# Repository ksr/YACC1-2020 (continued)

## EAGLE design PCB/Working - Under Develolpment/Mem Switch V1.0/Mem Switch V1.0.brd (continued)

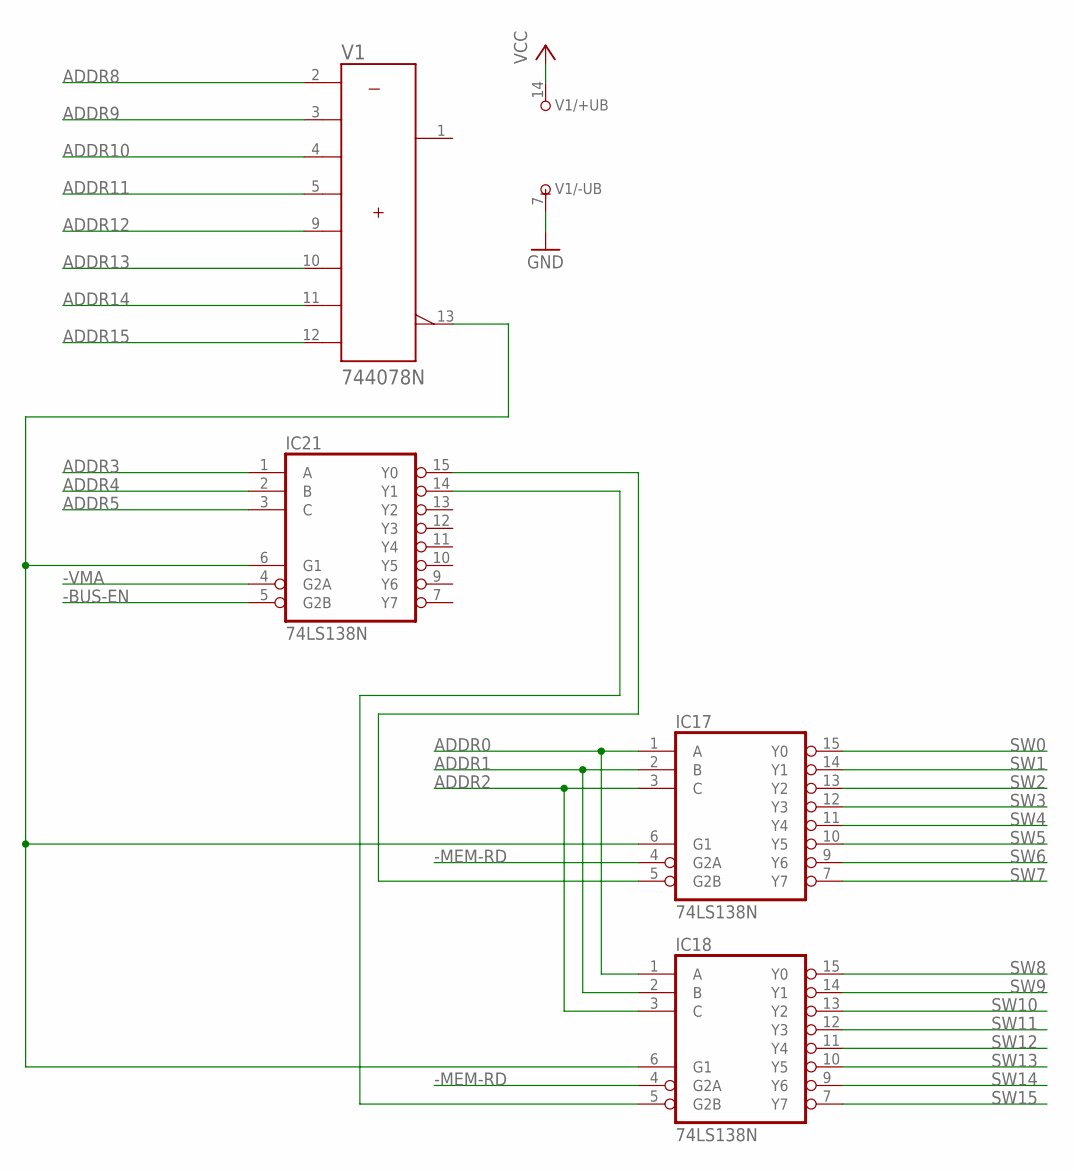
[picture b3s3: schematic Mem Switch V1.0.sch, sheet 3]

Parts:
IC17, IC18, IC21: 74LS138N; DIL16
V1: 744078N; DIL14

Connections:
-BUS-EN: IC21.5 (G2B); also elsewhere on the board
-MEM-RD: IC17.4 (G2A), IC18.4 (G2A); also elsewhere on the board
-VMA: IC21.4 (G2A); also elsewhere on the board
ADDR0: IC17.1 (A), IC18.1 (A); also elsewhere on the board
ADDR1: IC17.2 (B), IC18.2 (B); also elsewhere on the board
ADDR2: IC17.3 (C), IC18.3 (C); also elsewhere on the board
ADDR3: IC21.1 (A); also elsewhere on the board
ADDR4: IC21.2 (B); also elsewhere on the board
ADDR5: IC21.3 (C); also elsewhere on the board
ADDR8: V1.2 (A); also elsewhere on the board
ADDR9: V1.3 (B); also elsewhere on the board
ADDR10: V1.4 (C); also elsewhere on the board
ADDR11: V1.5 (D); also elsewhere on the board
ADDR12: V1.9 (E); also elsewhere on the board
ADDR13: V1.10 (F); also elsewhere on the board
ADDR14: V1.11 (G); also elsewhere on the board
ADDR15: V1.12 (H); also elsewhere on the board
GND: IC17.8 (GND), IC18.8 (GND), IC21.8 (GND), V1.7 (-UB); also elsewhere on the board
unnamed: IC17.5 (G2B), IC21.15 (Y0)
unnamed: IC18.5 (G2B), IC21.14 (Y1)
unnamed: IC17.6 (G1), IC18.6 (G1), IC21.6 (G1), V1.13 (W)
SW0: IC17.15 (Y0); also elsewhere on the board
SW1: IC17.14 (Y1); also elsewhere on the board
SW2: IC17.13 (Y2); also elsewhere on the board
SW3: IC17.12 (Y3); also elsewhere on the board
SW4: IC17.11 (Y4); also elsewhere on the board
SW5: IC17.10 (Y5); also elsewhere on the board
SW6: IC17.9 (Y6); also elsewhere on the board
SW7: IC17.7 (Y7); also elsewhere on the board
SW8: IC18.15 (Y0); also elsewhere on the board
SW9: IC18.14 (Y1); also elsewhere on the board
SW10: IC18.13 (Y2); also elsewhere on the board
SW11: IC18.12 (Y3); also elsewhere on the board
SW12: IC18.11 (Y4); also elsewhere on the board
SW13: IC18.10 (Y5); also elsewhere on the board
SW14: IC18.9 (Y6); also elsewhere on the board
SW15: IC18.7 (Y7); also elsewhere on the board
VCC: IC17.16 (VCC), IC18.16 (VCC), IC21.16 (VCC), V1.14 (+UB); also elsewhere on the board

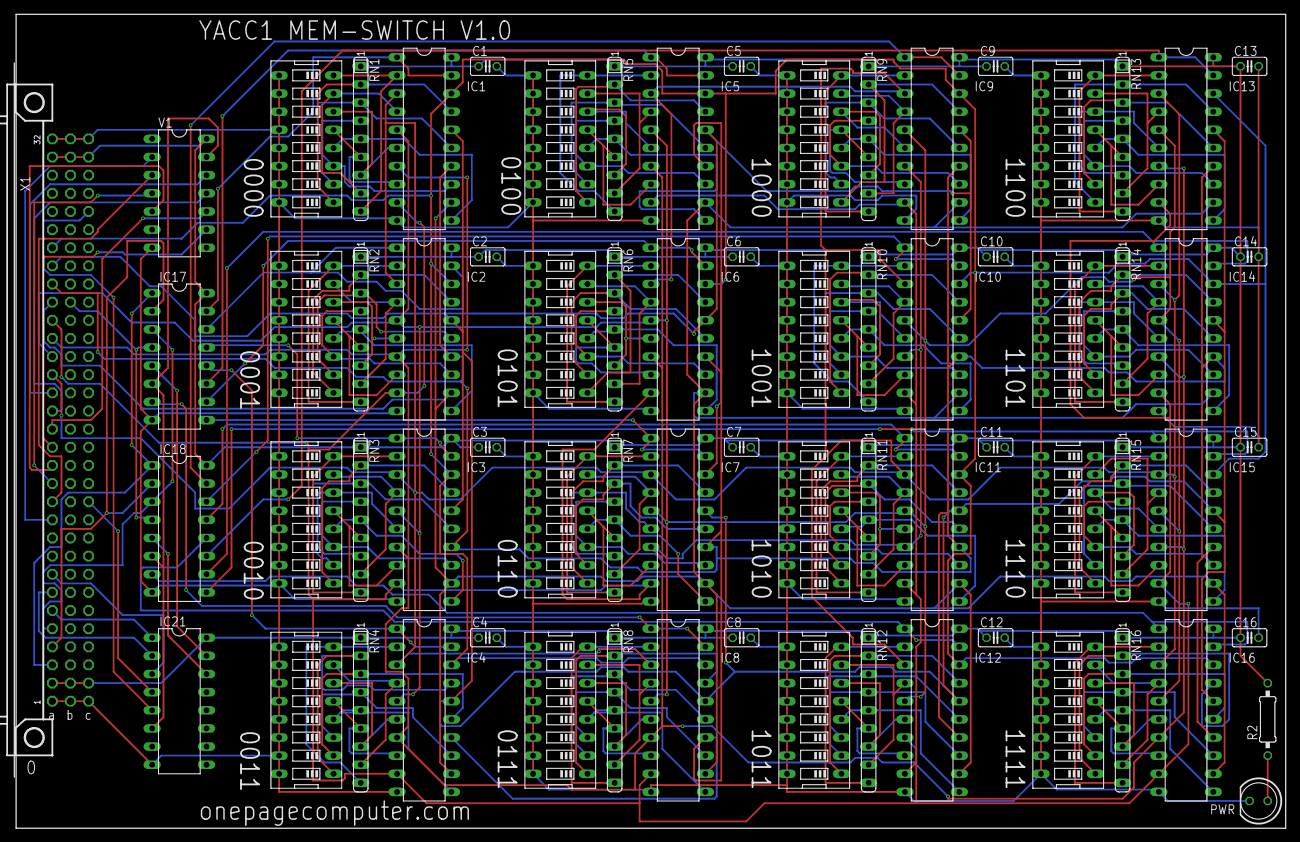
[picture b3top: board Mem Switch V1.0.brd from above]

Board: 2 copper layers, 177.8 x 114.0 mm, 71 parts (0 on the bottom side), 175 nets.

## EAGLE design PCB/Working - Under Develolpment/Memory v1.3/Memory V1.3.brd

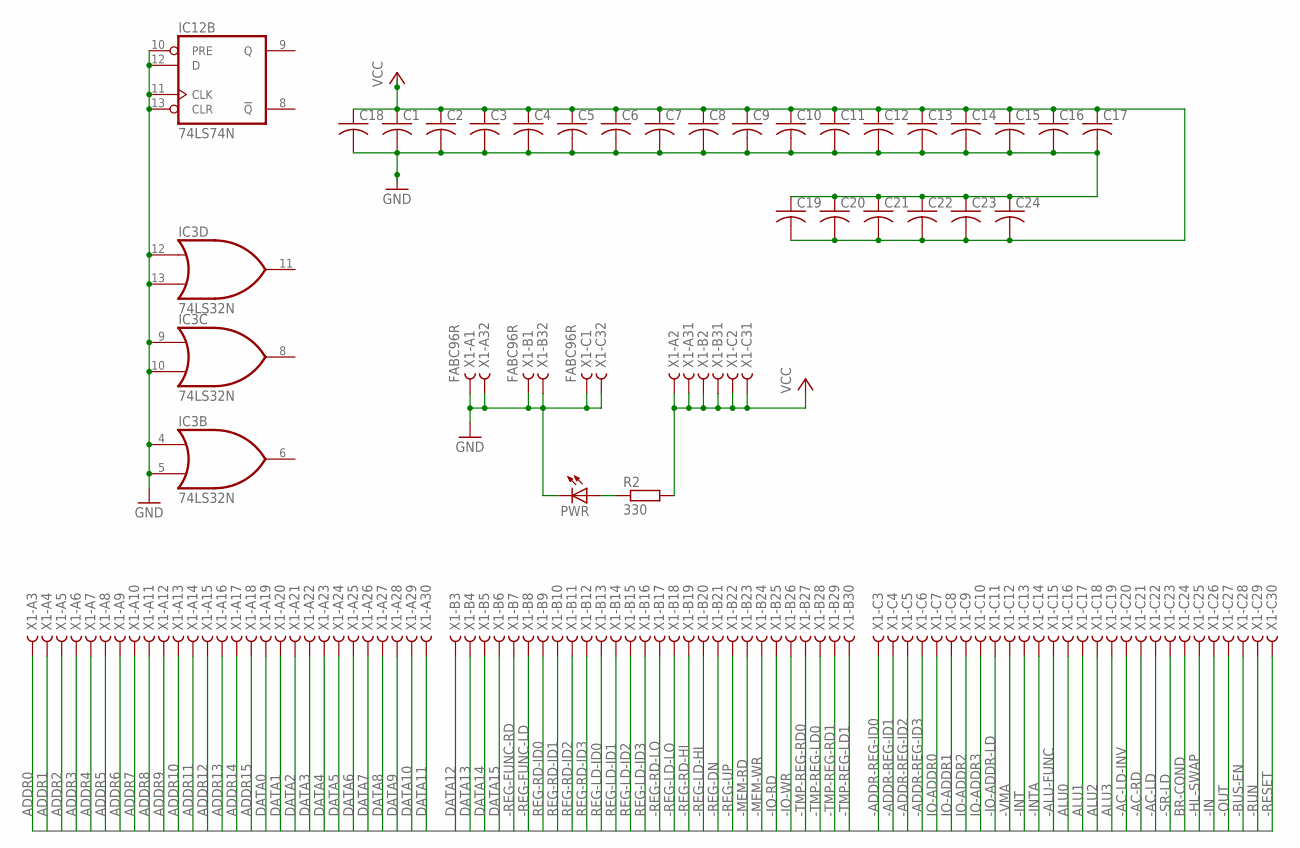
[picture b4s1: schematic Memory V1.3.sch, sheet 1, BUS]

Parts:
C1, C2, C3, C4, C5, C6, C7, C8, C9, C10, C11, C12, C13, C14, C15, C16, C17, C18, C19, C20, C21, C22, C23, C24: C-US025-025X050; C025-025X050
IC3: 74LS32N; DIL14
IC12: 74LS74N; DIL14
PWR: LED5MM
R2: 330; 0207/10
X1: FABC96R

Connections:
-AC-LD: X1.C22
-AC-LD-INV: X1.C20
-AC-RD: X1.C21
-ADDR-REG-ID0: X1.C3
-ADDR-REG-ID1: X1.C4
-ADDR-REG-ID2: X1.C5
-ADDR-REG-ID3: X1.C6
-ALU-FUNC: X1.C15
-BUS-EN: X1.C28; also elsewhere on the board
-HL-SWAP: X1.C25
-IN: X1.C26
-INT: X1.C13
-INTA: X1.C14
-IO-ADDR-LD: X1.C11
-IO-RD: X1.B25
-IO-WR: X1.B26
-MEM-RD: X1.B23; also elsewhere on the board
-MEM-WR: X1.B24; also elsewhere on the board
-OUT: X1.C27
-REG-DN: X1.B21
-REG-FUNC-LD: X1.B8
-REG-FUNC-RD: X1.B7
-REG-LD-HI: X1.B20
-REG-LD-LO: X1.B18
-REG-RD-HI: X1.B19
-REG-RD-LO: X1.B17
-REG-UP: X1.B22
-RESET: X1.C30; also elsewhere on the board
-RUN: X1.C29
-SR-LD: X1.C23
-TMP-REG-LD0: X1.B28; also elsewhere on the board
-TMP-REG-LD1: X1.B30; also elsewhere on the board
-TMP-REG-RD0: X1.B27; also elsewhere on the board
-TMP-REG-RD1: X1.B29; also elsewhere on the board
-VMA: X1.C12; also elsewhere on the board
ADDR0: X1.A3; also elsewhere on the board
ADDR1: X1.A4; also elsewhere on the board
ADDR2: X1.A5; also elsewhere on the board
ADDR3: X1.A6; also elsewhere on the board
ADDR4: X1.A7; also elsewhere on the board
ADDR5: X1.A8; also elsewhere on the board
ADDR6: X1.A9; also elsewhere on the board
ADDR7: X1.A10; also elsewhere on the board
ADDR8: X1.A11; also elsewhere on the board
ADDR9: X1.A12; also elsewhere on the board
ADDR10: X1.A13; also elsewhere on the board
ADDR11: X1.A14; also elsewhere on the board
ADDR12: X1.A15; also elsewhere on the board
ADDR13: X1.A16; also elsewhere on the board
ADDR14: X1.A17; also elsewhere on the board
ADDR15: X1.A18; also elsewhere on the board
ALU0: X1.C16
ALU1: X1.C17
ALU2: X1.C18
ALU3: X1.C19
BR-COND: X1.C24
DATA0: X1.A19; also elsewhere on the board
DATA1: X1.A20; also elsewhere on the board
DATA2: X1.A21; also elsewhere on the board
DATA3: X1.A22; also elsewhere on the board
DATA4: X1.A23; also elsewhere on the board
DATA5: X1.A24; also elsewhere on the board
DATA6: X1.A25; also elsewhere on the board
DATA7: X1.A26; also elsewhere on the board
DATA8: X1.A27; also elsewhere on the board
DATA9: X1.A28; also elsewhere on the board
DATA10: X1.A29; also elsewhere on the board
DATA11: X1.A30; also elsewhere on the board
DATA12: X1.B3; also elsewhere on the board
DATA13: X1.B4; also elsewhere on the board
DATA14: X1.B5; also elsewhere on the board
DATA15: X1.B6; also elsewhere on the board
GND: C1.2, C2.2, C3.2, C4.2, C5.2, C6.2, C7.2, C8.2, C9.2, C10.2, C11.2, C12.2, C13.2, C14.2, C15.2, C16.2, C17.2, C18.2, C19.1, C20.1, C21.1, C22.1, C23.1, C24.1, IC3.4 (I0), IC3.5 (I1), IC3.7 (GND), IC3.9 (I0), IC3.10 (I1), IC3.12 (I0), IC3.13 (I1), IC12.7 (GND), IC12.10 (PRE), IC12.11 (CLK), IC12.12 (D), IC12.13 (CLR), PWR.K (C), X1.A1, X1.A32, X1.B1, X1.B32, X1.C1, X1.C32; also elsewhere on the board
IO-ADDR0: X1.C7
IO-ADDR1: X1.C8
IO-ADDR2: X1.C9
IO-ADDR3: X1.C10
unnamed: PWR.A, R2.1
REG-LD-ID0: X1.B13
REG-LD-ID1: X1.B14
REG-LD-ID2: X1.B15
REG-LD-ID3: X1.B16
REG-RD-ID0: X1.B9
REG-RD-ID1: X1.B10
REG-RD-ID2: X1.B11
REG-RD-ID3: X1.B12
VCC: C1.1, C2.1, C3.1, C4.1, C5.1, C6.1, C7.1, C8.1, C9.1, C10.1, C11.1, C12.1, C13.1, C14.1, C15.1, C16.1, C17.1, C18.1, C19.2, C20.2, C21.2, C22.2, C23.2, C24.2, IC3.14 (VCC), IC12.14 (VCC), R2.2, X1.A2, X1.A31, X1.B2, X1.B31, X1.C2, X1.C31; also elsewhere on the board

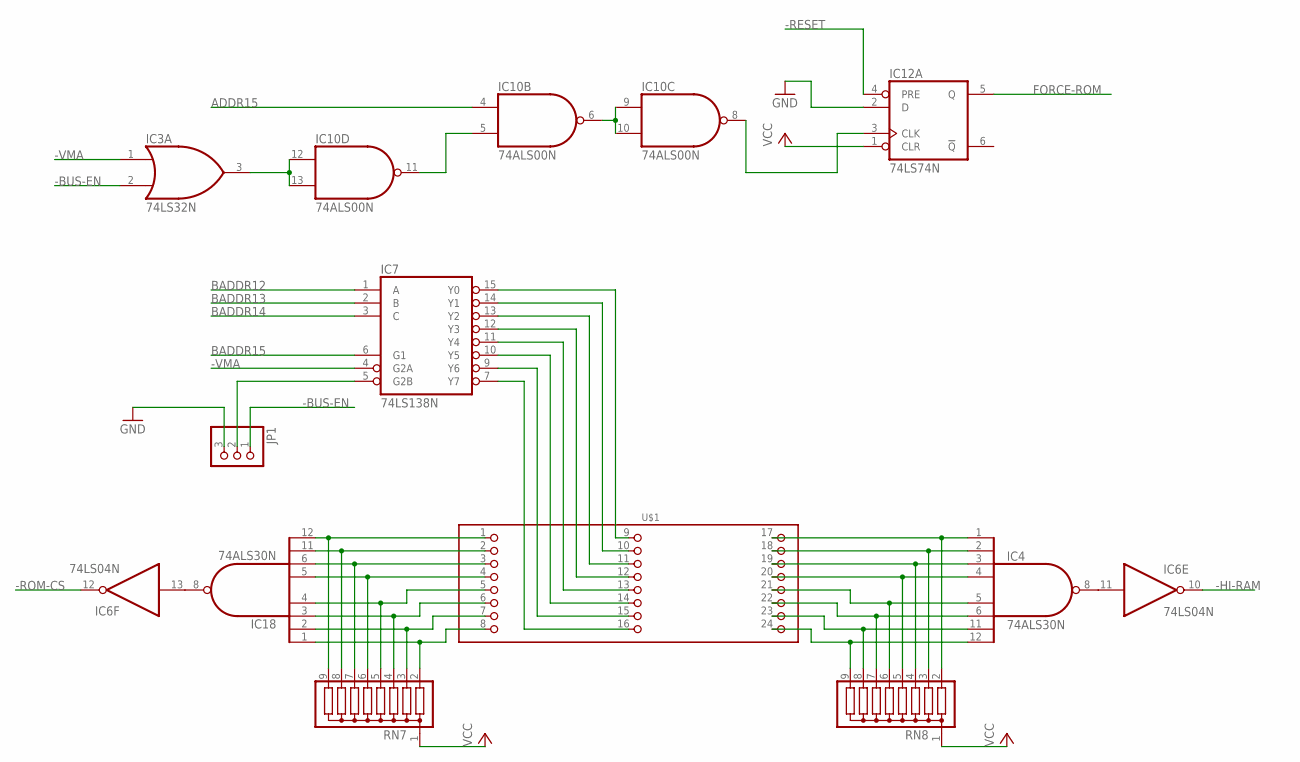
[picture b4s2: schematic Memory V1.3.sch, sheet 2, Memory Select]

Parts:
IC3: 74LS32N; DIL14
IC4, IC18: 74ALS30N; DIL14
IC6: 74LS04N; DIL14
IC7: 74LS138N; DIL16
IC10: 74ALS00N; DIL14
IC12: 74LS74N; DIL14
JP1: PINHD-1X3; 1X03
RN7, RN8: G08R; SIL9
U$1: PIN_3X8

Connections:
-BUS-EN: IC3.2 (I1), JP1.1; also elsewhere on the board
-HI-RAM: IC6.10 (O); also elsewhere on the board
-RESET: IC12.4 (PRE); also elsewhere on the board
-ROM-CS: IC6.12 (O); also elsewhere on the board
-VMA: IC3.1 (I0), IC7.4 (G2A); also elsewhere on the board
ADDR15: IC10.4 (I0); also elsewhere on the board
BADDR12: IC7.1 (A); also elsewhere on the board
BADDR13: IC7.2 (B); also elsewhere on the board
BADDR14: IC7.3 (C); also elsewhere on the board
BADDR15: IC7.6 (G1); also elsewhere on the board
FORCE-ROM: IC12.5 (Q); also elsewhere on the board
GND: IC3.7 (GND), IC4.7 (GND), IC6.7 (GND), IC7.8 (GND), IC10.7 (GND), IC12.2 (D), IC12.7 (GND), IC18.7 (GND), JP1.3; also elsewhere on the board
unnamed: IC6.13 (I), IC18.8 (O)
unnamed: IC4.1 (I0), RN8.2, U$1.17
unnamed: IC4.2 (I1), RN8.3, U$1.18
unnamed: IC4.3 (I2), RN8.4, U$1.19
unnamed: IC4.4 (I3), RN8.5, U$1.20
unnamed: IC4.5 (I4), RN8.6, U$1.21
unnamed: IC4.6 (I5), RN8.7, U$1.22
unnamed: IC4.8 (O), IC6.11 (I)
unnamed: IC10.8 (O), IC12.3 (CLK)
unnamed: IC10.6 (O), IC10.9 (I0), IC10.10 (I1)
unnamed: IC10.5 (I1), IC10.11 (O)
unnamed: IC7.5 (G2B), JP1.2
unnamed: IC3.3 (O), IC10.12 (I0), IC10.13 (I1)
unnamed: IC4.11 (I6), RN8.8, U$1.23
unnamed: IC4.12 (I7), RN8.9, U$1.24
unnamed: IC18.12 (I7), RN7.9, U$1.1
unnamed: IC18.11 (I6), RN7.8, U$1.2
unnamed: IC18.6 (I5), RN7.7, U$1.3
unnamed: IC18.5 (I4), RN7.6, U$1.4
unnamed: IC18.1 (I0), RN7.2, U$1.8
unnamed: IC18.2 (I1), RN7.3, U$1.7
unnamed: IC18.3 (I2), RN7.4, U$1.6
unnamed: IC7.7 (Y7), U$1.16
unnamed: IC7.9 (Y6), U$1.15
unnamed: IC7.10 (Y5), U$1.14
unnamed: IC7.11 (Y4), U$1.13
unnamed: IC7.12 (Y3), U$1.12
unnamed: IC7.13 (Y2), U$1.11
unnamed: IC7.14 (Y1), U$1.10
unnamed: IC7.15 (Y0), U$1.9
unnamed: IC18.4 (I3), RN7.5, U$1.5
VCC: IC3.14 (VCC), IC4.14 (VCC), IC6.14 (VCC), IC7.16 (VCC), IC10.14 (VCC), IC12.1 (CLR), IC12.14 (VCC), IC18.14 (VCC), RN7.1, RN8.1; also elsewhere on the board

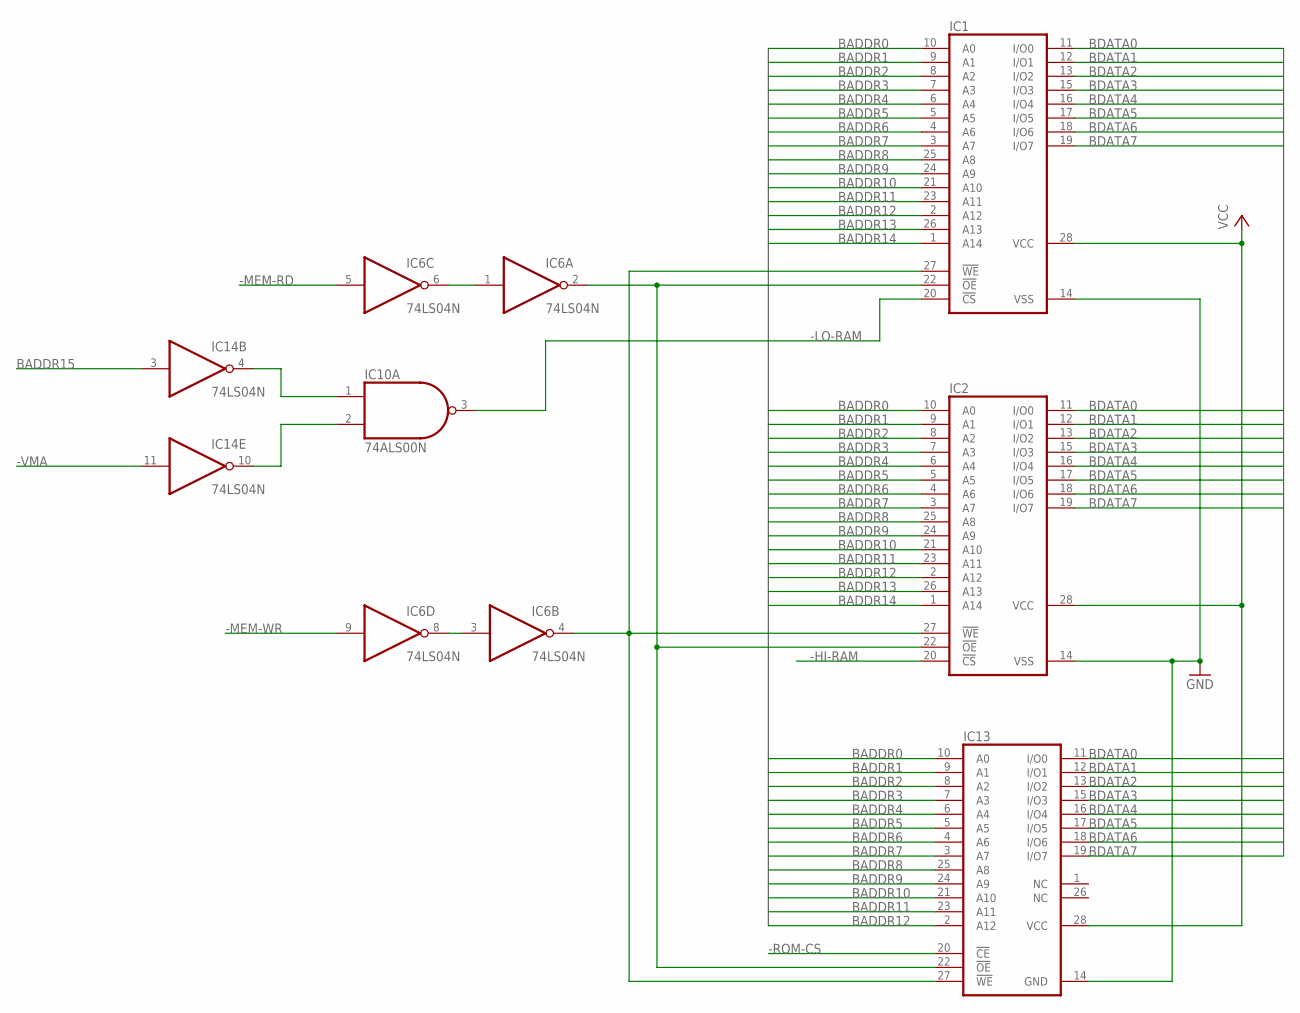
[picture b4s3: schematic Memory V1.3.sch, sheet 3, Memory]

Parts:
IC1, IC2: 62256P; DIL28-6
IC6, IC14: 74LS04N; DIL14
IC10: 74ALS00N; DIL14
IC13: 28C64C; DIL28-6

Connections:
-HI-RAM: IC2.20 (!CS); also elsewhere on the board
-LO-RAM: IC1.20 (!CS), IC10.3 (O)
-MEM-RD: IC6.5 (I); also elsewhere on the board
-MEM-WR: IC6.9 (I); also elsewhere on the board
-ROM-CS: IC13.20 (!CE); also elsewhere on the board
-VMA: IC14.11 (I); also elsewhere on the board
BADDR0: IC1.10 (A0), IC2.10 (A0), IC13.10 (A0); also elsewhere on the board
BADDR1: IC1.9 (A1), IC2.9 (A1), IC13.9 (A1); also elsewhere on the board
BADDR2: IC1.8 (A2), IC2.8 (A2), IC13.8 (A2); also elsewhere on the board
BADDR3: IC1.7 (A3), IC2.7 (A3), IC13.7 (A3); also elsewhere on the board
BADDR4: IC1.6 (A4), IC2.6 (A4), IC13.6 (A4); also elsewhere on the board
BADDR5: IC1.5 (A5), IC2.5 (A5), IC13.5 (A5); also elsewhere on the board
BADDR6: IC1.4 (A6), IC2.4 (A6), IC13.4 (A6); also elsewhere on the board
BADDR7: IC1.3 (A7), IC2.3 (A7), IC13.3 (A7); also elsewhere on the board
BADDR8: IC1.25 (A8), IC2.25 (A8), IC13.25 (A8); also elsewhere on the board
BADDR9: IC1.24 (A9), IC2.24 (A9), IC13.24 (A9); also elsewhere on the board
BADDR10: IC1.21 (A10), IC2.21 (A10), IC13.21 (A10); also elsewhere on the board
BADDR11: IC1.23 (A11), IC2.23 (A11), IC13.23 (A11); also elsewhere on the board
BADDR12: IC1.2 (A12), IC2.2 (A12), IC13.2 (A12); also elsewhere on the board
BADDR13: IC1.26 (A13), IC2.26 (A13); also elsewhere on the board
BADDR14: IC1.1 (A14), IC2.1 (A14); also elsewhere on the board
BADDR15: IC14.3 (I); also elsewhere on the board
BDATA0: IC1.11 (I/O0), IC2.11 (I/O0), IC13.11 (I/O0); also elsewhere on the board
BDATA1: IC1.12 (I/O1), IC2.12 (I/O1), IC13.12 (I/O1); also elsewhere on the board
BDATA2: IC1.13 (I/O2), IC2.13 (I/O2), IC13.13 (I/O2); also elsewhere on the board
BDATA3: IC1.15 (I/O3), IC2.15 (I/O3), IC13.15 (I/O3); also elsewhere on the board
BDATA4: IC1.16 (I/O4), IC2.16 (I/O4), IC13.16 (I/O4); also elsewhere on the board
BDATA5: IC1.17 (I/O5), IC2.17 (I/O5), IC13.17 (I/O5); also elsewhere on the board
BDATA6: IC1.18 (I/O6), IC2.18 (I/O6), IC13.18 (I/O6); also elsewhere on the board
BDATA7: IC1.19 (I/O7), IC2.19 (I/O7), IC13.19 (I/O7); also elsewhere on the board
GND: IC1.14 (VSS), IC2.14 (VSS), IC6.7 (GND), IC10.7 (GND), IC13.14 (GND), IC14.7 (GND); also elsewhere on the board
MEM-RD: IC6.1 (I), IC6.6 (O)
unnamed: IC6.3 (I), IC6.8 (O)
unnamed: IC1.22 (!OE), IC2.22 (!OE), IC6.2 (O), IC13.22 (!OE)
unnamed: IC1.27 (!WE), IC2.27 (!WE), IC6.4 (O), IC13.27 (!WE)
unnamed: IC10.2 (I1), IC14.10 (O)
unnamed: IC10.1 (I0), IC14.4 (O)
VCC: IC1.28 (VCC), IC2.28 (VCC), IC6.14 (VCC), IC10.14 (VCC), IC13.28 (VCC), IC14.14 (VCC); also elsewhere on the board

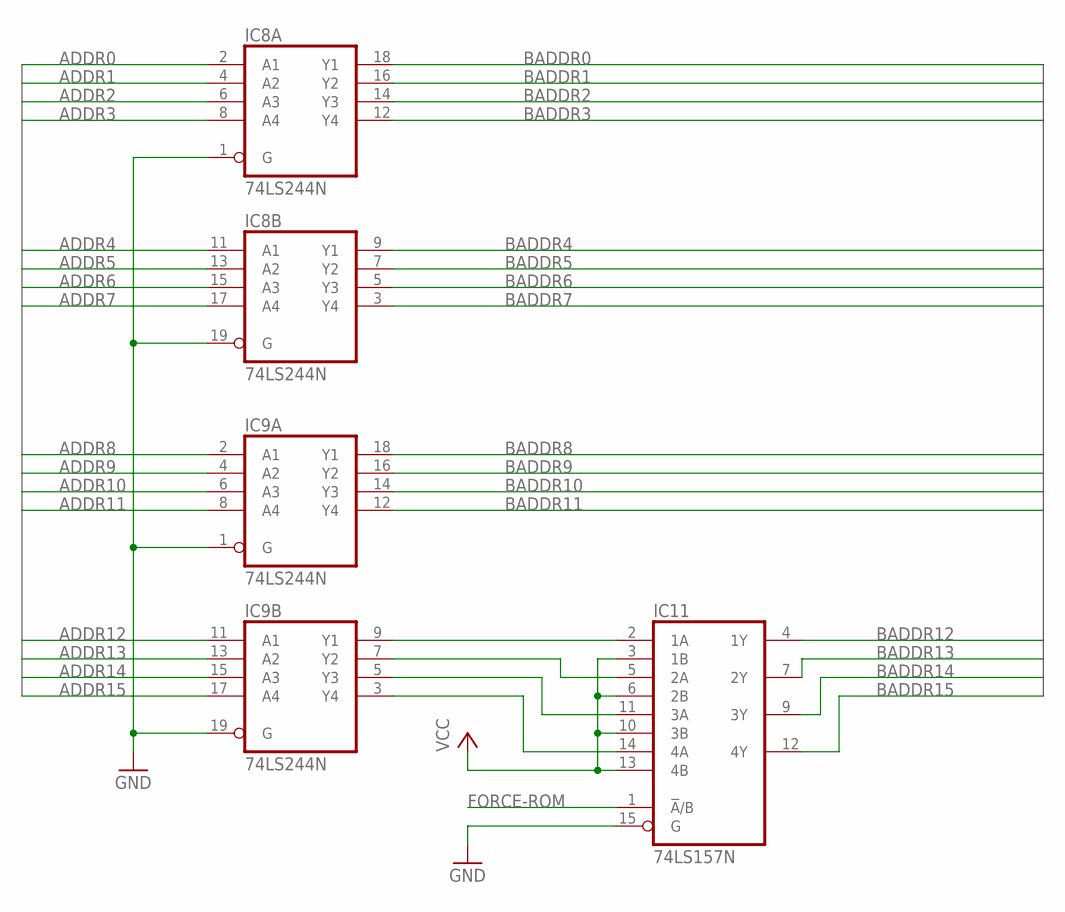
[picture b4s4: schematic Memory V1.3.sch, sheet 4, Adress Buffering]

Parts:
IC8, IC9: 74LS244N; DIL20
IC11: 74LS157N; DIL16

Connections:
ADDR0: IC8.2 (A1); also elsewhere on the board
ADDR1: IC8.4 (A2); also elsewhere on the board
ADDR2: IC8.6 (A3); also elsewhere on the board
ADDR3: IC8.8 (A4); also elsewhere on the board
ADDR4: IC8.11 (A1); also elsewhere on the board
ADDR5: IC8.13 (A2); also elsewhere on the board
ADDR6: IC8.15 (A3); also elsewhere on the board
ADDR7: IC8.17 (A4); also elsewhere on the board
ADDR8: IC9.2 (A1); also elsewhere on the board
ADDR9: IC9.4 (A2); also elsewhere on the board
ADDR10: IC9.6 (A3); also elsewhere on the board
ADDR11: IC9.8 (A4); also elsewhere on the board
ADDR12: IC9.11 (A1); also elsewhere on the board
ADDR13: IC9.13 (A2); also elsewhere on the board
ADDR14: IC9.15 (A3); also elsewhere on the board
ADDR15: IC9.17 (A4); also elsewhere on the board
BADDR0: IC8.18 (Y1); also elsewhere on the board
BADDR1: IC8.16 (Y2); also elsewhere on the board
BADDR2: IC8.14 (Y3); also elsewhere on the board
BADDR3: IC8.12 (Y4); also elsewhere on the board
BADDR4: IC8.9 (Y1); also elsewhere on the board
BADDR5: IC8.7 (Y2); also elsewhere on the board
BADDR6: IC8.5 (Y3); also elsewhere on the board
BADDR7: IC8.3 (Y4); also elsewhere on the board
BADDR8: IC9.18 (Y1); also elsewhere on the board
BADDR9: IC9.16 (Y2); also elsewhere on the board
BADDR10: IC9.14 (Y3); also elsewhere on the board
BADDR11: IC9.12 (Y4); also elsewhere on the board
BADDR12: IC11.4 (1Y); also elsewhere on the board
BADDR13: IC11.7 (2Y); also elsewhere on the board
BADDR14: IC11.9 (3Y); also elsewhere on the board
BADDR15: IC11.12 (4Y); also elsewhere on the board
FORCE-ROM: IC11.1 (!A!/B); also elsewhere on the board
GND: IC8.1 (G), IC8.10 (GND), IC8.19 (G), IC9.1 (G), IC9.10 (GND), IC9.19 (G), IC11.8 (GND), IC11.15 (G); also elsewhere on the board
unnamed: IC9.9 (Y1), IC11.2 (1A)
unnamed: IC9.7 (Y2), IC11.5 (2A)
unnamed: IC9.5 (Y3), IC11.11 (3A)
unnamed: IC9.3 (Y4), IC11.14 (4A)
VCC: IC8.20 (VCC), IC9.20 (VCC), IC11.3 (1B), IC11.6 (2B), IC11.10 (3B), IC11.13 (4B), IC11.16 (VCC); also elsewhere on the board

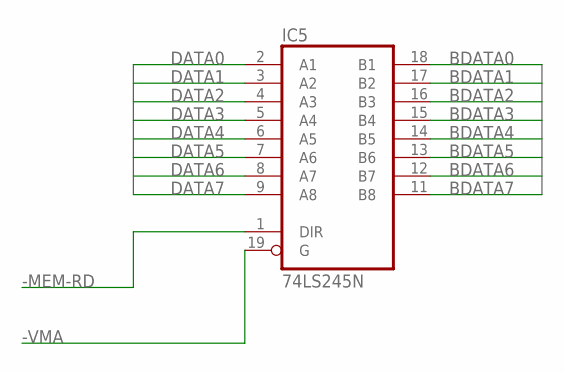
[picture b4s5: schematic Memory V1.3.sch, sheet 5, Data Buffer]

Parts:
IC5: 74LS245N; DIL20

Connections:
-MEM-RD: IC5.1 (DIR); also elsewhere on the board
-VMA: IC5.19 (G); also elsewhere on the board
BDATA0: IC5.18 (B1); also elsewhere on the board
BDATA1: IC5.17 (B2); also elsewhere on the board
BDATA2: IC5.16 (B3); also elsewhere on the board
BDATA3: IC5.15 (B4); also elsewhere on the board
BDATA4: IC5.14 (B5); also elsewhere on the board
BDATA5: IC5.13 (B6); also elsewhere on the board
BDATA6: IC5.12 (B7); also elsewhere on the board
BDATA7: IC5.11 (B8); also elsewhere on the board
DATA0: IC5.2 (A1); also elsewhere on the board
DATA1: IC5.3 (A2); also elsewhere on the board
DATA2: IC5.4 (A3); also elsewhere on the board
DATA3: IC5.5 (A4); also elsewhere on the board
DATA4: IC5.6 (A5); also elsewhere on the board
DATA5: IC5.7 (A6); also elsewhere on the board
DATA6: IC5.8 (A7); also elsewhere on the board
DATA7: IC5.9 (A8); also elsewhere on the board
GND: IC5.10 (GND); also elsewhere on the board
VCC: IC5.20 (VCC); also elsewhere on the board

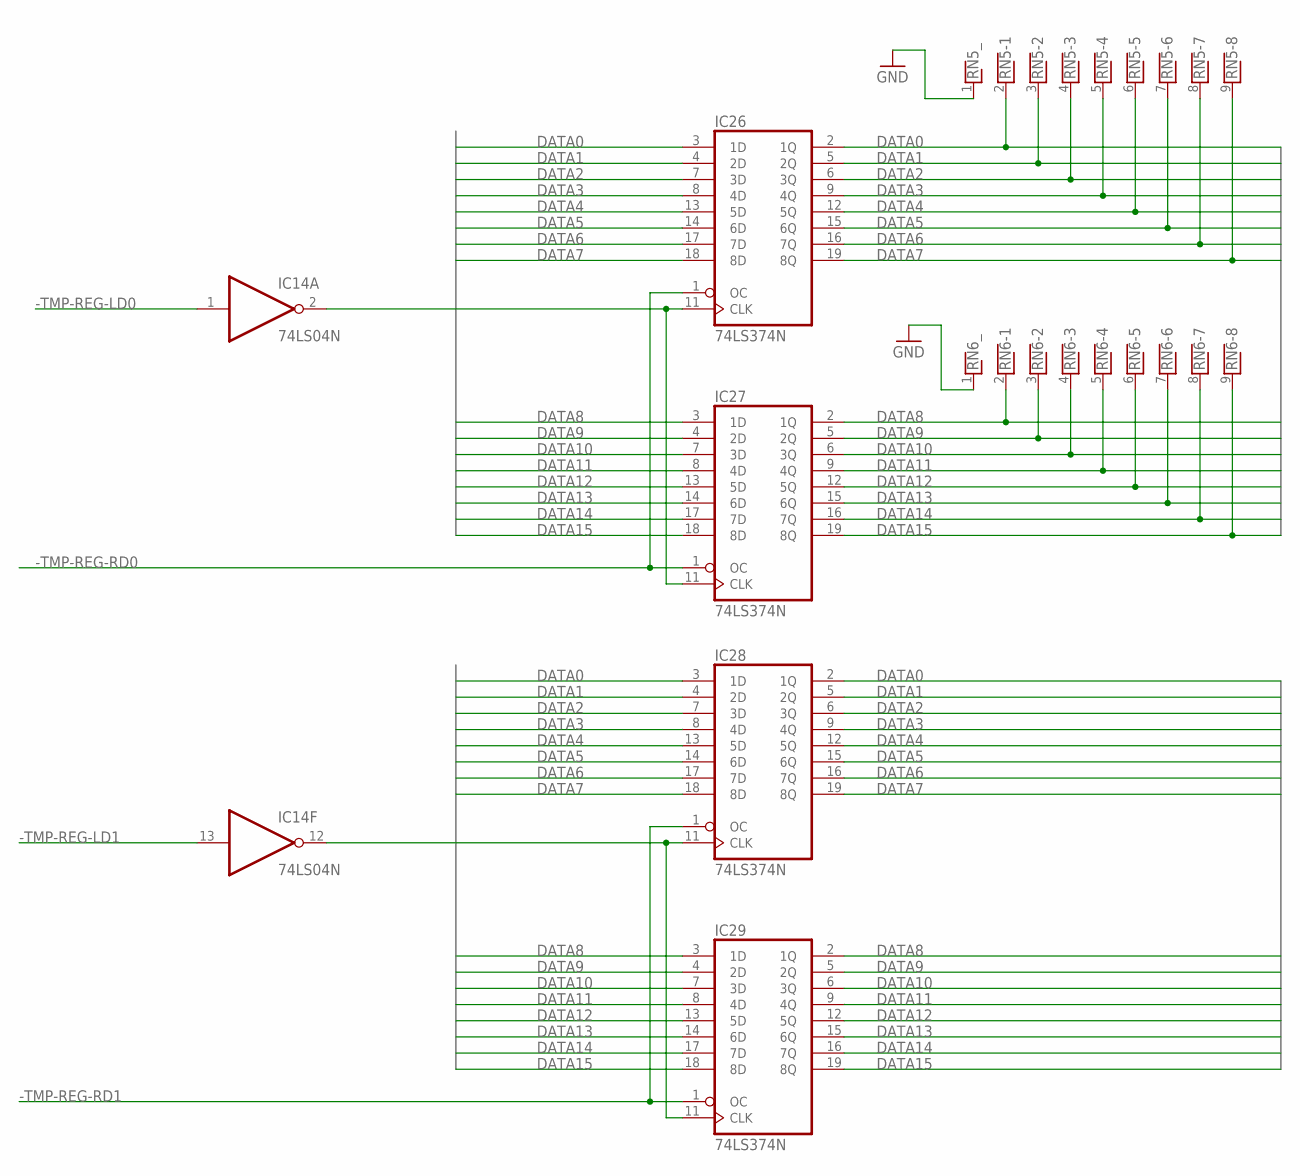
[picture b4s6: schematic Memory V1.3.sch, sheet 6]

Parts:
IC14: 74LS04N; DIL14
IC26, IC27, IC28, IC29: 74LS374N; DIL20
RN5, RN6: RNX8; RN-9

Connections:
-TMP-REG-LD0: IC14.1 (I); also elsewhere on the board
-TMP-REG-LD1: IC14.13 (I); also elsewhere on the board
-TMP-REG-RD0: IC26.1 (OC), IC27.1 (OC); also elsewhere on the board
-TMP-REG-RD1: IC28.1 (OC), IC29.1 (OC); also elsewhere on the board
DATA0: IC26.2 (1Q), IC26.3 (1D), IC28.2 (1Q), IC28.3 (1D), RN5.2; also elsewhere on the board
DATA1: IC26.4 (2D), IC26.5 (2Q), IC28.4 (2D), IC28.5 (2Q), RN5.3; also elsewhere on the board
DATA2: IC26.6 (3Q), IC26.7 (3D), IC28.6 (3Q), IC28.7 (3D), RN5.4; also elsewhere on the board
DATA3: IC26.8 (4D), IC26.9 (4Q), IC28.8 (4D), IC28.9 (4Q), RN5.5; also elsewhere on the board
DATA4: IC26.12 (5Q), IC26.13 (5D), IC28.12 (5Q), IC28.13 (5D), RN5.6; also elsewhere on the board
DATA5: IC26.14 (6D), IC26.15 (6Q), IC28.14 (6D), IC28.15 (6Q), RN5.7; also elsewhere on the board
DATA6: IC26.16 (7Q), IC26.17 (7D), IC28.16 (7Q), IC28.17 (7D), RN5.8; also elsewhere on the board
DATA7: IC26.18 (8D), IC26.19 (8Q), IC28.18 (8D), IC28.19 (8Q), RN5.9; also elsewhere on the board
DATA8: IC27.2 (1Q), IC27.3 (1D), IC29.2 (1Q), IC29.3 (1D), RN6.2; also elsewhere on the board
DATA9: IC27.4 (2D), IC27.5 (2Q), IC29.4 (2D), IC29.5 (2Q), RN6.3; also elsewhere on the board
DATA10: IC27.6 (3Q), IC27.7 (3D), IC29.6 (3Q), IC29.7 (3D), RN6.4; also elsewhere on the board
DATA11: IC27.8 (4D), IC27.9 (4Q), IC29.8 (4D), IC29.9 (4Q), RN6.5; also elsewhere on the board
DATA12: IC27.12 (5Q), IC27.13 (5D), IC29.12 (5Q), IC29.13 (5D), RN6.6; also elsewhere on the board
DATA13: IC27.14 (6D), IC27.15 (6Q), IC29.14 (6D), IC29.15 (6Q), RN6.7; also elsewhere on the board
DATA14: IC27.16 (7Q), IC27.17 (7D), IC29.16 (7Q), IC29.17 (7D), RN6.8; also elsewhere on the board
DATA15: IC27.18 (8D), IC27.19 (8Q), IC29.18 (8D), IC29.19 (8Q), RN6.9; also elsewhere on the board
GND: IC14.7 (GND), IC26.10 (GND), IC27.10 (GND), IC28.10 (GND), IC29.10 (GND), RN5.1, RN6.1; also elsewhere on the board
unnamed: IC14.2 (O), IC26.11 (CLK), IC27.11 (CLK)
unnamed: IC14.12 (O), IC28.11 (CLK), IC29.11 (CLK)
VCC: IC14.14 (VCC), IC26.20 (VCC), IC27.20 (VCC), IC28.20 (VCC), IC29.20 (VCC); also elsewhere on the board

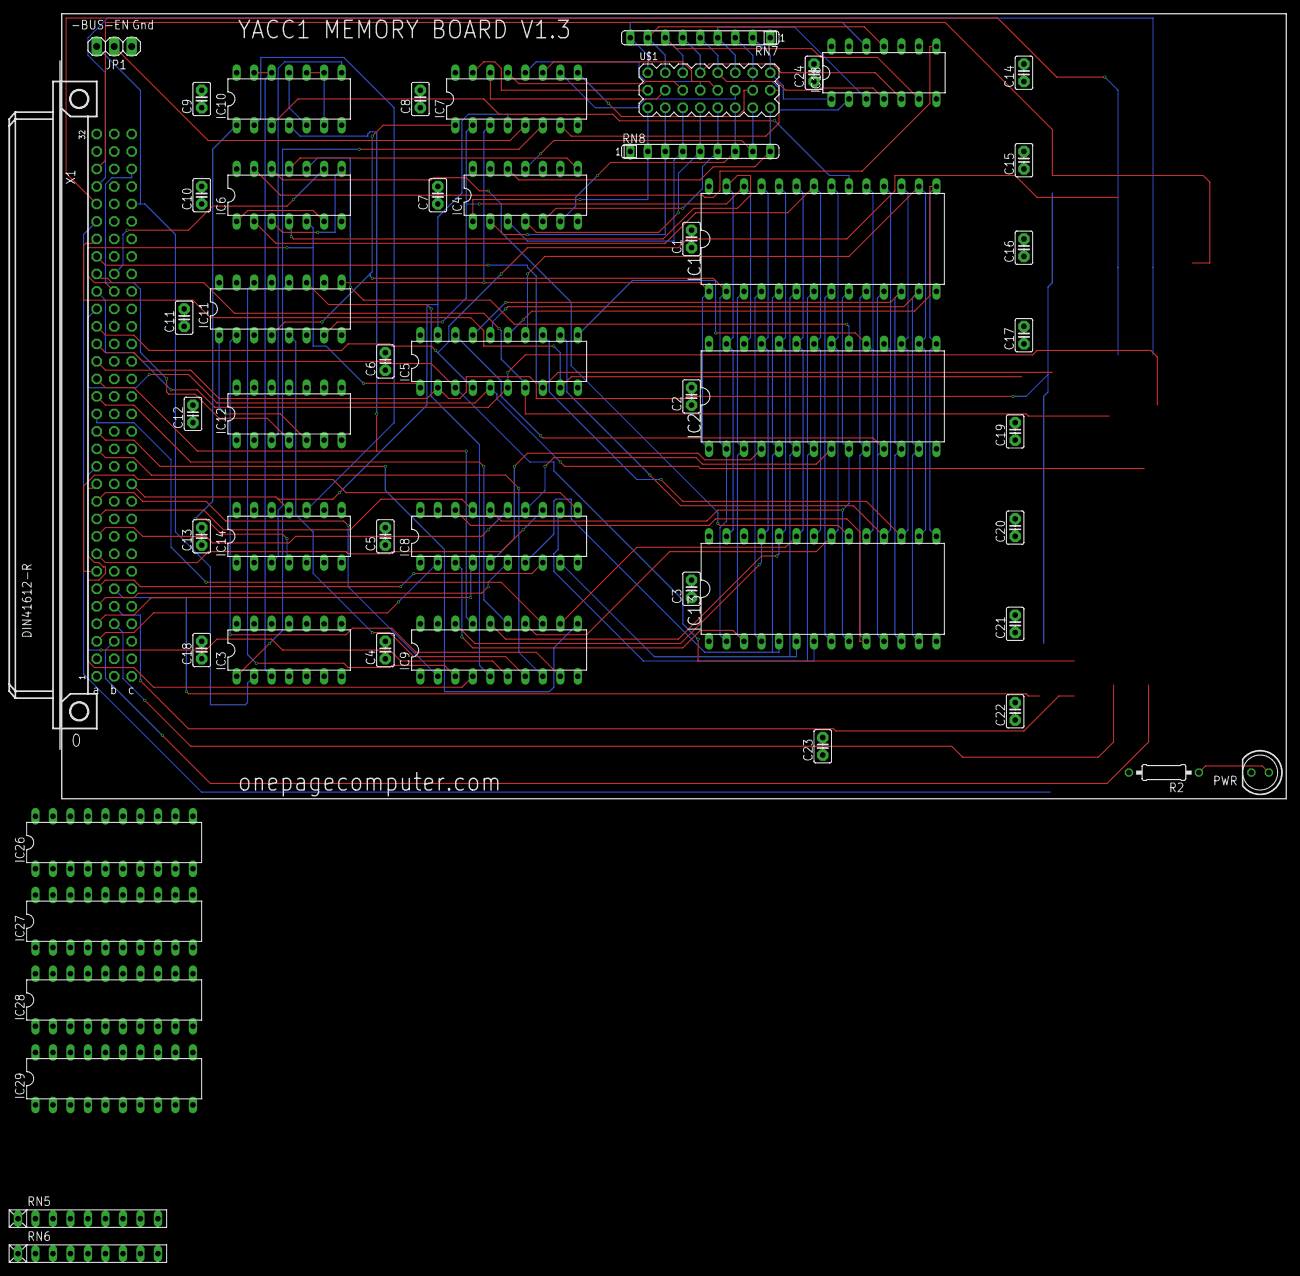
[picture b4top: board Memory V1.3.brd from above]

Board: 4 copper layers, 177.8 x 114.0 mm, 52 parts (0 on the bottom side), 115 nets.
